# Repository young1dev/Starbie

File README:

# Starbie

Starbie is a tiny motion-controlled digital pet — essentially a desktop Tamagotchi with minimal gameplay buttons. Instead of relying entirely on button presses, you interact with the pet by moving the device.

Built around the Seeed XIAO ESP32-C3, Starbie uses an OLED display to bring the pet to life and motion input to respond to interactions. My version adds a vibration motor for physical feedback and a custom PCB designed to integrate the electronics used.

The PCB design and firmware are complete, but the PCB has not yet been tested.

## What It Is

Starbie is designed to sit on your desk, display its personality on a small screen, and react to how you handle it. Its interface combines a tilt-controlled radial menu, pet animations, and a stats screen.

The custom PCB integrates the microcontroller, display connections, buttons, sensors, and additional circuitry for vibration feedback. The design incorporates both through-hole and surface-mount components.

## Why?

This project was created as my Week 1 project for [Half Life](https://halflife.hackclub.com/?ref=2639), a 10 weeks hardware-building program.

My goal was to adapt the original design and add a physical response to the pet's interactions through a vibration motor and its driver circuit.

## Project Status

The KiCad design files, PCB renders, and firmware are included in this repository.

The firmware targets the Seeed XIAO ESP32-C3 and uses PlatformIO with the Arduino framework. It includes the virtual pet interface, tilt-controlled radial menu, stats screen, and shake interaction, with vibration feedback added as my custom feature.

**Current status:** The PCB design and firmware are complete. The physical PCB has not yet been assembled and tested, so the operation of the complete hardware remains unverified.

## Hardware

The design includes the following main components:

- **Microcontroller:** Seeed XIAO ESP32-C3
- **Display:** 128 × 64, 0.96-inch I²C OLED
- **Environmental sensor:** DHT11 temperature and humidity sensor
- **Motion sensing:** MPU6050, as used by the firmware
- **Physical feedback:** DC vibration motor
- **Motor driver:** AO3400A N-channel MOSFET and SS14 Schottky diode
- **Controls:** Two push buttons
- **Power:** Main battery and JST-PH battery connector
- **Additional components:** Resistors, connectors, and supporting circuitry

See the `Hardware/` directory for the KiCad schematic and PCB design files. Consult the component list and schematic for the circuit connections and power requirements before assembling the board.

## Software

The firmware is maintained as a separate PlatformIO project in [`Firmware/`](Firmware/).

See [`Firmware/README.md`](Firmware/README.md) for the development environment, build and upload instructions, controls, and sprite customization guide.

## Repository Contents

- [`Hardware/`](Hardware/) — KiCad schematic and PCB source files.
- [`Images/`](Images/) — PCB renders and design screenshots.
- [`Firmware/`](Firmware/) — PlatformIO firmware project.

## Credits

Starbie builds on the original project documented in the [Starbie Week 1 Guide](https://github.com/SharKingStudios/Starbie/blob/main/Week%201%20Guide.md).

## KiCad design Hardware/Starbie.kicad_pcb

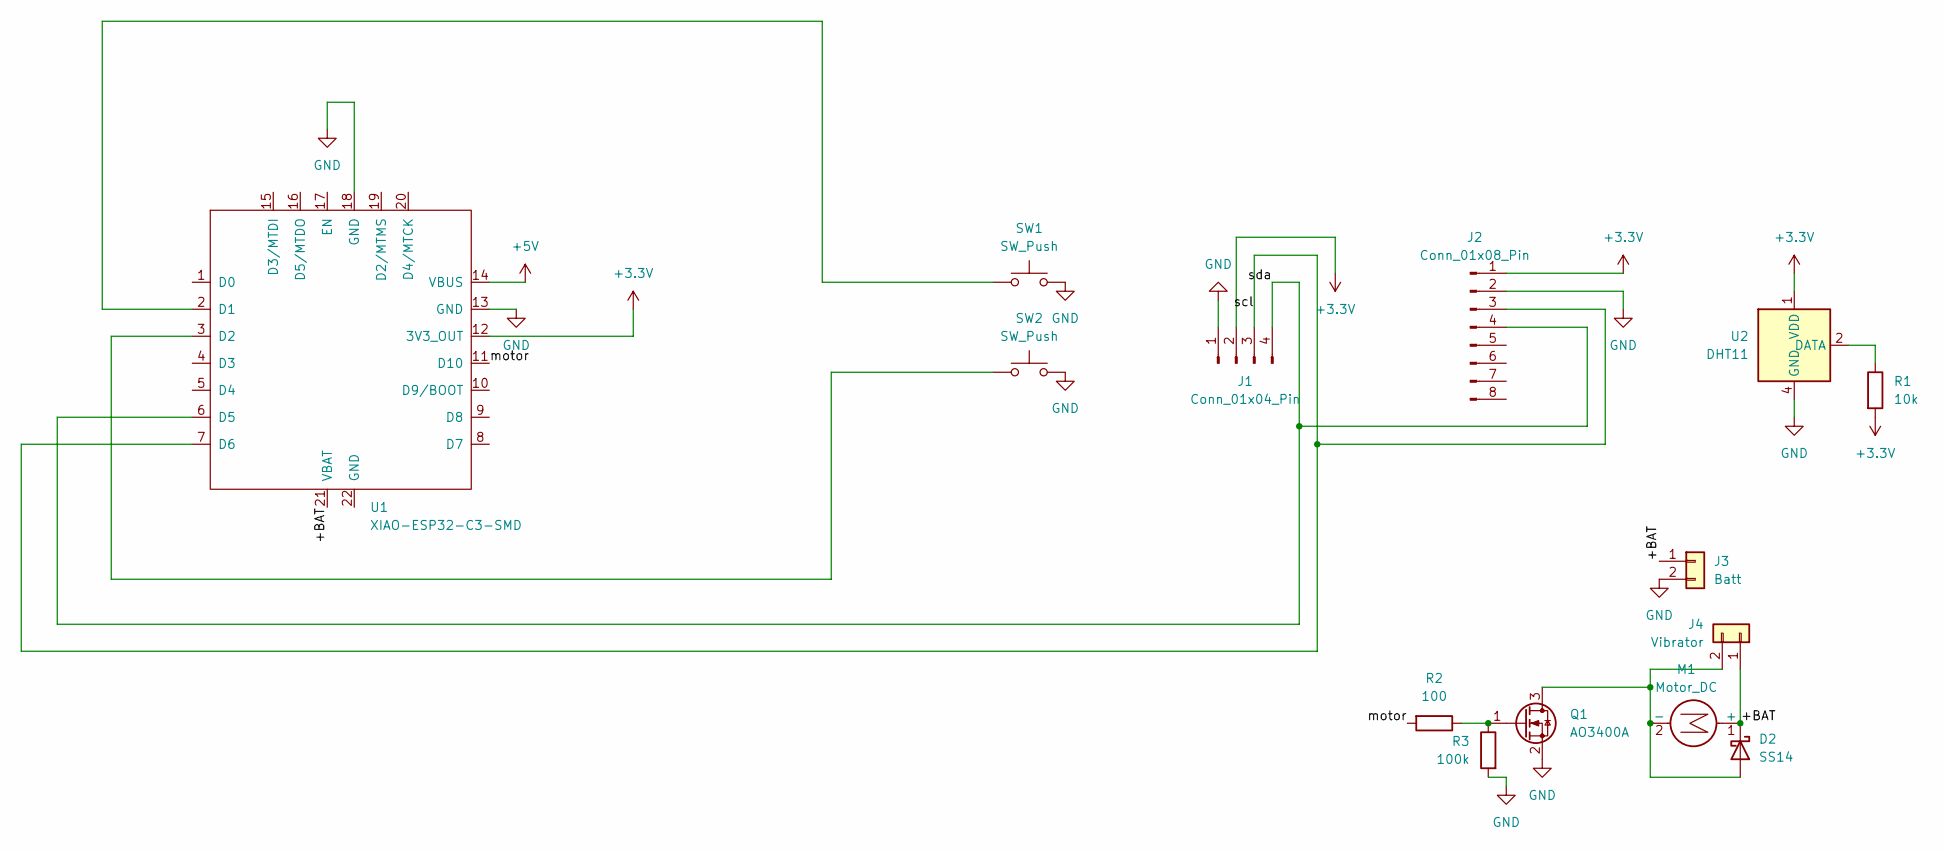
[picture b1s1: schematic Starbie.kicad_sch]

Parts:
D2: SS14; D_SMA
J1: Conn_01x04_Pin; Display_128x64_096_I2C
J2: Conn_01x08_Pin; PinHeader_1x08_P2.54mm_Vertical
J3: Batt; JST_PH_S2B-PH-K_1x02_P2.00mm_Horizontal
J4: Vibrator; JST_PH_S2B-PH-K_1x02_P2.00mm_Horizontal
M1: Motor_DC
Q1: AO3400A; SOT-23
R1: 10k; R_Axial_DIN0204_L3.6mm_D1.6mm_P7.62mm_Horizontal
R2: 100; R_Axial_DIN0204_L3.6mm_D1.6mm_P7.62mm_Horizontal
R3: 100k; R_Axial_DIN0204_L3.6mm_D1.6mm_P7.62mm_Horizontal
SW1, SW2: SW_Push; SW_Cherry_MX_1.00u_PCB
U1: XIAO-ESP32-C3-SMD
U2: DHT11; Aosong_DHT11_5.5x12.0_P2.54mm

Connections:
+3.3V: J1.2, J2.1, R1.2, U1.12 (3V3_OUT), U2.1 (VDD)
+5V: U1.14 (VBUS)
/+BAT: D2.1 (K), J3.1, J4.1, M1.1 (+), U1.21 (VBAT)
/motor: R2.2, U1.11 (D10)
/scl: J1.3, J2.3, U1.7 (D6)
/sda: J1.4, J2.4, U1.6 (D5)
GND: J1.1, J2.2, J3.2, Q1.2 (S), R3.2, SW1.2, SW2.2, U1.13 (GND), U1.18 (GND), U2.4 (GND)
unnamed: D2.2 (A), J4.2, M1.2 (-), Q1.3 (D)
unnamed: Q1.1 (G), R2.1, R3.1
unnamed: SW1.1, U1.2 (D1)
unnamed: SW2.1, U1.3 (D2)
unnamed: R1.1, U2.2 (DATA)

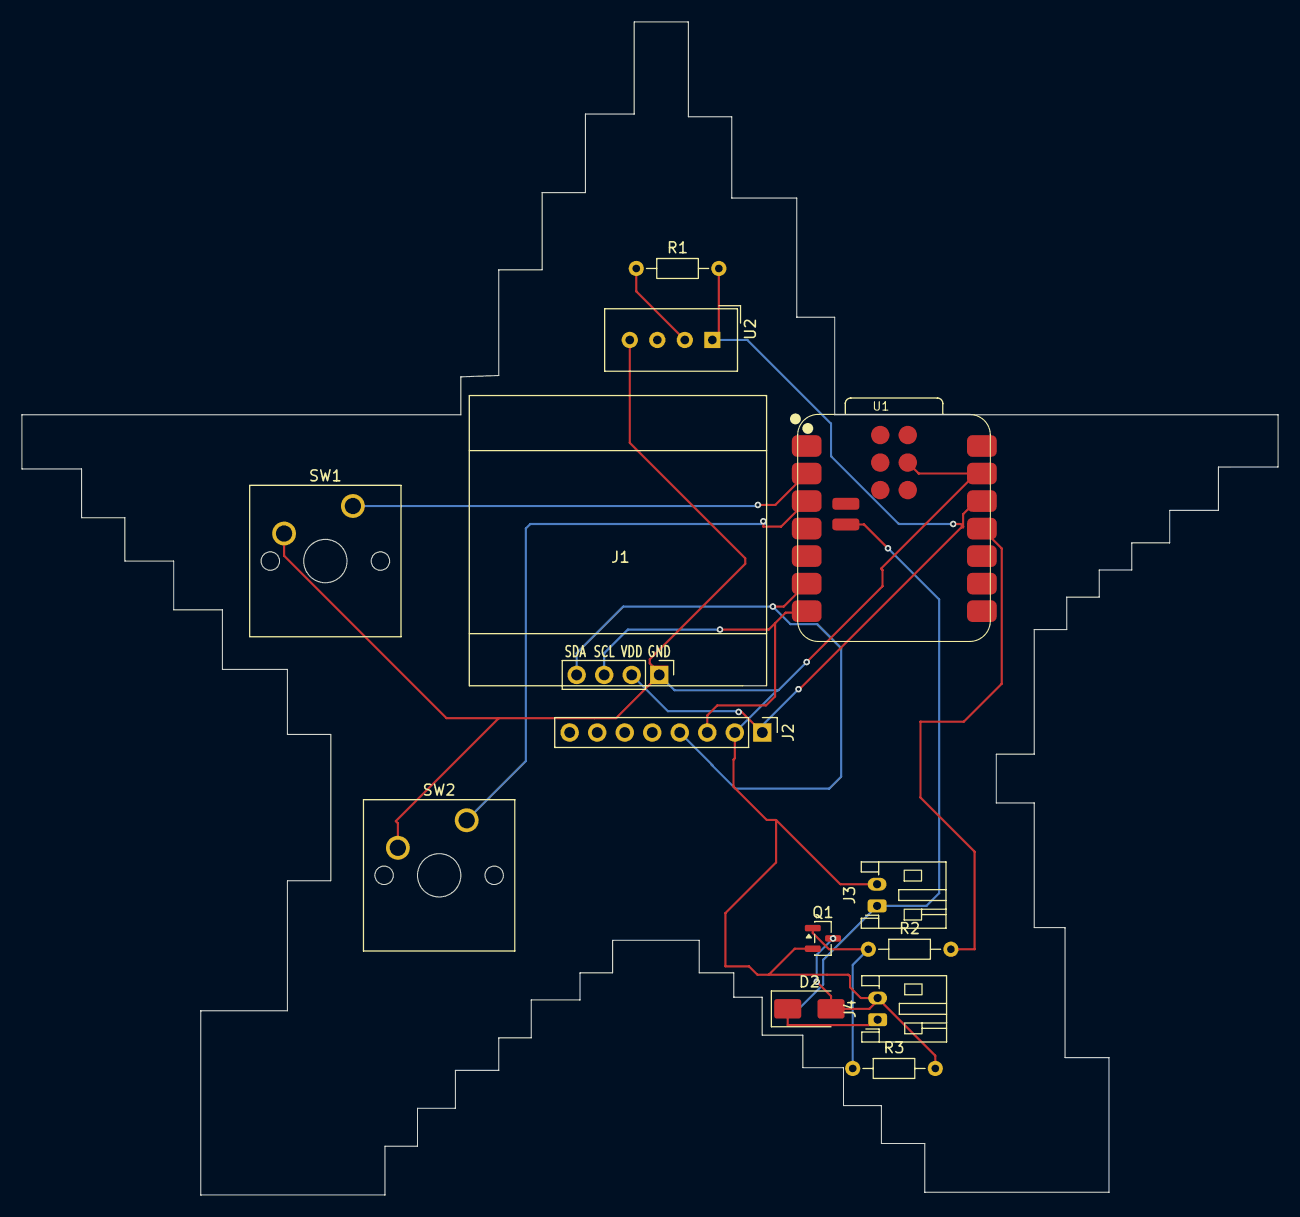
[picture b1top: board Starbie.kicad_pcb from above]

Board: 2 copper layers, 115.9 x 108.2 mm, 13 parts (0 on the bottom side), 11 nets.
